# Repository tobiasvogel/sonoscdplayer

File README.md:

# SonosCDPlayer

**Your CDs, straight to Sonos.**

SonosCDPlayer is an open-source DIY project for building a standalone audio CD player that streams music to Sonos speakers over a local network.

It brings together the familiar experience of a physical CD player and the convenience of network audio: insert a disc, select your Sonos speakers, and control playback using dedicated buttons and a compact display.

The project uses readily available components, including a single-board computer, an optical drive, and configurable hardware controls. The long-term goal is a reliable, easy-to-use CD player that works without a smartphone or separate app during everyday operation.

## Project status

**Functional prototype — active development**

SonosCDPlayer is no longer just a concept. A working Python implementation exists, and its core audio, playback, Sonos, and hardware-interface functionality has been tested on real equipment.

Current capabilities include:

- **Live CD playback:** Read audio CDs and stream digital audio to Sonos over the local network.
- **Playback control:** Play, pause, resume, stop, next, and previous, including hardware-tested physical buttons.
- **Sonos integration:** Discover and select speakers, with controlled playback on individual devices and temporary speaker groups.
- **Display interface:** Show playback status, navigate menus, and select Sonos speakers using physical controls.
- **RAM-only audio buffering:** Stream CD audio using bounded memory without creating persistent audio copies.
- **Disc management:** Detect disc changes, handle verified USB drive reconnection, and eject discs using a physical button on tested hardware.
- **CD metadata and artwork:** Read CD-TEXT, retrieve MusicBrainz metadata, and store metadata and cover images in a local cache.
- **Wi-Fi setup:** Configure a network on the device or through a temporary setup hotspot.
- **System services:** Run the player and hardware interfaces through local services with configurable behaviour.

These foundations are implemented, but not every feature is enabled by default or validated across different hardware combinations. First-time setup, some device controls, broader hardware compatibility, and long-term reliability still require additional work.

**This is a working prototype, not yet a finished plug-and-play product or a complete beginner installation guide.**

## Design goals

- **Physical-first operation:** Dedicated controls and a display should make everyday playback feel like using a conventional CD player.
- **Local playback:** Play audio CDs through Sonos over the local network without requiring a cloud music service.
- **No ripping required:** Listen to physical CDs without first building a digital music library.
- **Respect existing Sonos playback:** Avoid unexpectedly interrupting other sources or changing unrelated speaker groups.
- **Accessible DIY hardware:** Use standard components and support different enclosure designs and hardware configurations.
- **Simple, maintainable software:** Prefer practical solutions, clear component boundaries, and predictable behaviour.

SonosCDPlayer is intended to be a dedicated CD player, not a general-purpose Sonos management system.

## How it works

The player reads digital audio from an inserted CD, buffers it in memory, and serves it as a WAV-compatible HTTP audio stream over the local network. The selected Sonos speaker or group retrieves this stream directly from the player.

```text
Audio CD -> Optical drive -> CD-DA reader -> Bounded RAM buffer
                                               |
                                               v
                                         Local HTTP server
                                               |
                                               v
                                         Sonos playback

Physical controls -> Player controller -> Display UI and menus
                              |
                              +-> Disc and drive management
                              |
                              +-> Sonos discovery and control
```

The player controller coordinates playback state, track navigation, disc handling, and Sonos control. Local interfaces allow hardware components to communicate with the player.

Audio is streamed as 44.1 kHz, 16-bit stereo PCM in a WAV-compatible format. The implementation includes buffering and HTTP range handling. Normal playback does not create persistent CD audio files.

## Hardware

SonosCDPlayer is designed around readily available components so builders can choose hardware that suits their needs and enclosure designs.

The software is developed and tested primarily on a Raspberry Pi 4 reference setup, while the architecture aims to accommodate different configurations.

A typical build consists of:

| Component | Purpose |
| --- | --- |
| Single-board computer (SBC), such as a Raspberry Pi | Runs the player software and network services |
| CD/DVD optical drive | Reads standard audio CDs |
| Sonos speaker or group | Receives and plays the CD audio stream |
| Display module | Shows playback information, device status, and menus |
| Physical controls (buttons and/or rotary encoder) | Control playback, navigate menus, and select options |
| Status LEDs (optional) | Provide additional visual feedback |
| Ambient light sensor (optional) | Enables automatic display and LED brightness adjustment |
| Power supply and enclosure | Complete the physical player |

### Hardware compatibility

The reference build combines physical buttons and a rotary encoder on a custom PCB, but alternative control layouts are a design goal. The repository also contains 3D-printable enclosure parts; a complete, tested assembly guide is still in preparation.

Reference optical drives are the **ASUS SDRW-08U1MT**, the **Panasonic/Matshita BD-MLT UJ265** and the **LG HL-DT-ST DVDRAM GTC0N**, each confirmed with the drive check below. Idle spin-down and wake-up were first verified with the ASUS drive connected through a powered USB hub. The **TSSTcorp CDDVDW TS-U633J** was also evaluated but proved unstable in the tested setup. These results are not an exhaustive compatibility list. To test another drive, run `python3 tools/check_drive.py` with an audio CD inserted; see [Checking a CD drive](docs/DRIVE_CHECK.md).

The [SonosCDPlayer website](https://sonoscdplayer.diy) is intended to collect tested components, hardware configurations, and community builds over time.

The goal is to support different builds, from simple functional prototypes to custom Hi-Fi components. Support for alternative SBCs, displays, and interfaces remains subject to implementation and testing.

## Playback and controls

SonosCDPlayer supports conventional CD playback controls through configurable physical input devices. The reference implementation combines dedicated buttons and a rotary encoder.

| Control | Behaviour |
| --- | --- |
| Play / Pause | Start, pause, or resume CD playback |
| Stop | Stop the player's CD playback and go back to track 1 |
| Next | Select or play the next track (stopped: counts up at once, without waking the drive) |
| Previous | Select or play the previous track (stopped: counts down at once, without waking the drive) |
| Eject | Open the drive tray when the required safety conditions are met |
| Volume + / − | Change the Sonos volume in steps of 1 (the whole group when grouped); hold to repeat. Works during the player's own playback, or before playback on a selected speaker that is not playing anything |
| Rotary encoder | Navigate the display interface |
| Encoder press | Confirm menu selections |

Physical playback buttons and disc ejection have been validated on reference hardware.

Volume buttons have been tested on reference hardware.

A Power button implementation provides a display-based power menu and long-press shutdown request. These system actions require explicit configuration.

**Important:** Hardware controls may run in diagnostic or preview modes unless their execution paths are enabled. A fresh installation does not automatically activate every available control function for now.

See [Power button](docs/POWER_BUTTON.md) for details.

## Sonos integration

SonosCDPlayer discovers available Sonos devices on the local network and provides a display-based interface for choosing a playback target.

Users can select an individual speaker or a combination of supported speakers. The player can create a temporary group for CD playback when the target devices are in an appropriate state. A disc-wide track queue enables navigation from the Sonos app; targeted hardware validation of the latest start and transition handling remains open.

Speaker selection and playback remain separate operations:

- Selecting speakers does not automatically start playback.
- The player checks the target state before taking control.
- Playback commands are restricted to the player's own active stream where appropriate.
- Unrelated playback sessions and groups must not be changed without explicit authorisation.
- Temporary groups created by the player are released again when playback ends; the player remembers them across restarts and cleans up a leftover of its own speakers at the next selection, PLAY or EJECT.
- A speaker chosen on the device that sits in an idle Sonos group (stopped or paused) is taken out of that group on its own; the rest of the group stays together. Groups that are playing are never changed.
- During playback, speakers can be added or removed in the device menu without interruption; choosing another main speaker restarts the current track on it. Changes made in the Sonos app are taken over and become the new speaker selection.
- Stereo pairs and home-theatre sets (Sub, surrounds) count as one speaker.

Individual-speaker playback and controlled group operation have been tested on real Sonos hardware. Compatibility with every Sonos model, firmware version, and network environment has not been established.

## Configuration

SonosCDPlayer uses **TOML configuration files** for software and hardware settings.

| File | Purpose |
| --- | --- |
| [`config/player.example.toml`](config/player.example.toml) | Audio streaming, optical drive management, and service settings |
| [`config/interface.example.toml`](config/interface.example.toml) | GPIO buttons, rotary encoder, and input behaviour |
| [`config/ui.example.toml`](config/ui.example.toml) | Display preferences and interface language |

The active configuration lives in **`/etc/sonoscdplayer/`** (`player.toml`, `interface.toml`, `ui.toml`); all services and tools read it from there. The repository files above are templates only. `tools/install_config.py` creates the files from the templates or migrates an existing configuration. See [Configuration files and location](docs/CONFIGURATION.md).

A configuration update utility offers dry-run checks, structural validation against an optional reference, backup creation, and rollback support. Perform service-affecting updates while the player is idle. See [Updating the player configuration](docs/CONFIG_UPDATE.md).

To join a Wi-Fi network, use the device menu to select a network and enter its password, or hold CONNECT for 10 seconds to open a temporary setup hotspot with a web page. Both methods have been tested on reference hardware; additional failure and timeout scenarios remain open. See [Wi-Fi setup](docs/NETWORK_SETUP.md).

## Display and languages

SonosCDPlayer provides a display-based interface for playback information, device status, and menu navigation.

The player supports the SSD1327 grayscale OLED and SSD1351 RGB OLED through the same `[display]` configuration. Both 128x128 modules have been tested on hardware; see [Display configuration](docs/DISPLAY_CONFIGURATION.md) and [SSD1351](docs/SSD1351.md). Drivers and test tools for a smaller monochrome OLED (SH1107) and a color LCD (ST7735S) are included and await their connection to the player; a four-color e-paper module was evaluated and found unsuitable. See [Displays](docs/DISPLAYS.md).

The implemented interface includes playback and disc status, interactive menus, Sonos target selection, and rotary encoder navigation. English and German are available; the selected language is retained across restarts in local application state. Adaptive brightness is supported on suitable reference hardware.

CD-TEXT, MusicBrainz metadata and album artwork on the reference OLED are implemented and have been tested on hardware. Further interface improvements and metadata edge-case testing remain open.

See [Display languages and translations](docs/I18N.md) for details.

## Development roadmap

The roadmap distinguishes working foundations from features still under development or awaiting broader validation.

### Working foundations

- [x] Detect audio CDs and read track information on reference hardware.
- [x] Stream live CD audio to a real Sonos device.
- [x] Implement bounded RAM-only audio buffering.
- [x] Implement playback state management and track navigation.
- [x] Provide a persistent player service and local control interface.
- [x] Implement Sonos discovery, target selection, and controlled temporary group playback.
- [x] Implement an interactive display interface with playback status and menus, validated on reference OLED hardware.
- [x] Implement and hardware-test physical playback buttons.
- [x] Detect disc changes and handle verified optical drive reconnection.
- [x] Implement and hardware-test physical disc ejection on reference hardware.
- [x] Verify optical-drive idle spin-down and wake-up using a powered USB hub on reference hardware.
- [x] Implement and hardware-test CD-TEXT, MusicBrainz lookup, and local metadata and cover caching.
- [x] Implement and hardware-test device-based Wi-Fi selection and setup hotspot.

### Work in progress and planned features

- [ ] Complete hardware validation of remaining device controls and their integration.
- [ ] Validate optical-drive idle spin-down and wake-up over extended operation and on additional hardware.
- [ ] Complete boot, shutdown, restart, and long-term reliability testing.
- [ ] Validate remaining Wi-Fi setup failure, timeout, and recovery scenarios.
- [ ] Complete hardware tests for disc-wide Sonos navigation and remaining metadata edge cases.
- [ ] Expand and validate support for additional hardware configurations and interchangeable interfaces.
- [ ] Publish reproducible installation instructions and a hardware compatibility guide.
- [ ] Provide a complete bill of materials, wiring documentation, and a tested build guide.

Completed items represent implemented and tested foundations, not universal hardware compatibility or completion of every related enhancement.

## Documentation

Additional documentation is available in the [`docs/`](docs/) directory.

| Document | Description |
| --- | --- |
| [Configuration files and location](docs/CONFIGURATION.md) | Standard location, installation, migration, and systemd units |
| [Configuration updates](docs/CONFIG_UPDATE.md) | TOML configuration checks, replacement, and rollback |
| [Display languages and translations](docs/I18N.md) | Language selection and adding translations |
| [Wi-Fi setup](docs/NETWORK_SETUP.md) | Joining a new Wi-Fi network through the setup hotspot |
| [Power button](docs/POWER_BUTTON.md) | Power controls, permissions, and activation |
| [Shutdown and restart screens](docs/SHUTDOWN_SCREENS.md) | OLED screens while shutting down or restarting, installation, optional exitrd |
| [Status LEDs](docs/STATUS_LEDS.md) | Meaning of the power and connection (network) LEDs |
| [Checking a CD drive](docs/DRIVE_CHECK.md) | Test whether a USB CD drive suits the player and share the result |
| [Displays](docs/DISPLAYS.md) | Supported and evaluated modules; [configuration](docs/DISPLAY_CONFIGURATION.md), [SSD1351](docs/SSD1351.md), [SH1107](docs/SH1107.md) and [ST7735S](docs/ST7735S.md) |
| [Architecture](docs/ARCHITECTURE.md) | Services, sockets, data flow and package layout, for developers |
| [Adding a display](docs/ADDING_A_DISPLAY.md) | Driver, test program, renderer and tests for a new display module |
| [Adding buttons and input modules](docs/ADDING_INPUTS.md) | New buttons, shift registers or other input modules, rotary encoder |
| [Releases and updates](docs/RELEASE.md) | Version number, making a release, updating the device |
| [Changelog](CHANGELOG.md) | Changes per version |

Some features are optional or hardware-specific. Consult each guide for its requirements and limitations.

## Contributing

Contributions are welcome, including software improvements, hardware compatibility reports, testing feedback, translations, wiring diagrams, documentation, and enclosure designs.

The Python code is one package, `src/sonoscdplayer/`, organized by area: `audio` (reading and streaming the CD), `drive` (the optical drive), `metadata`, `sonos`, `player` (the player service), `ui` (the display service and menu), `hardware` (displays, buttons, LEDs, sensors), `network_setup` and `system`. Native C code is in `src/native/`. Tests mirror the package under `tests/` and run with `python3 -m pytest`. Every public module, class and function has a docstring (Google style); run `tools/build_api_docs.sh` to turn them into an HTML code reference in `docs/api/` with [pdoc](https://pdoc.dev) (Debian package `python3-pdoc`, installed by `scripts/setup.sh`). Start with the [architecture overview](docs/ARCHITECTURE.md).

For substantial code changes, please open an issue describing the proposed improvement or problem before beginning work. The project favours maintainable implementations and incremental, hardware-backed testing.

Do not commit credentials, private network information, personal Sonos device identifiers, local configuration files containing private details, or copyrighted CD audio recordings.

## License

See [LICENSE](LICENSE) for the repository's GNU General Public License version 2 license text.

## Project links

**Website:** https://sonoscdplayer.diy  
**GitHub:** https://github.com/tobiasvogel/sonoscdplayer

## Disclaimer

SonosCDPlayer is an independent open-source community project and is not affiliated with, endorsed by, or sponsored by Sonos, Inc. Sonos is a trademark of its respective owner.

Hardware compatibility depends on the components, software versions, and network environment used. Not every configuration has been tested.

Product-style illustrations and renderings are conceptual unless explicitly identified as photographs of a tested build.

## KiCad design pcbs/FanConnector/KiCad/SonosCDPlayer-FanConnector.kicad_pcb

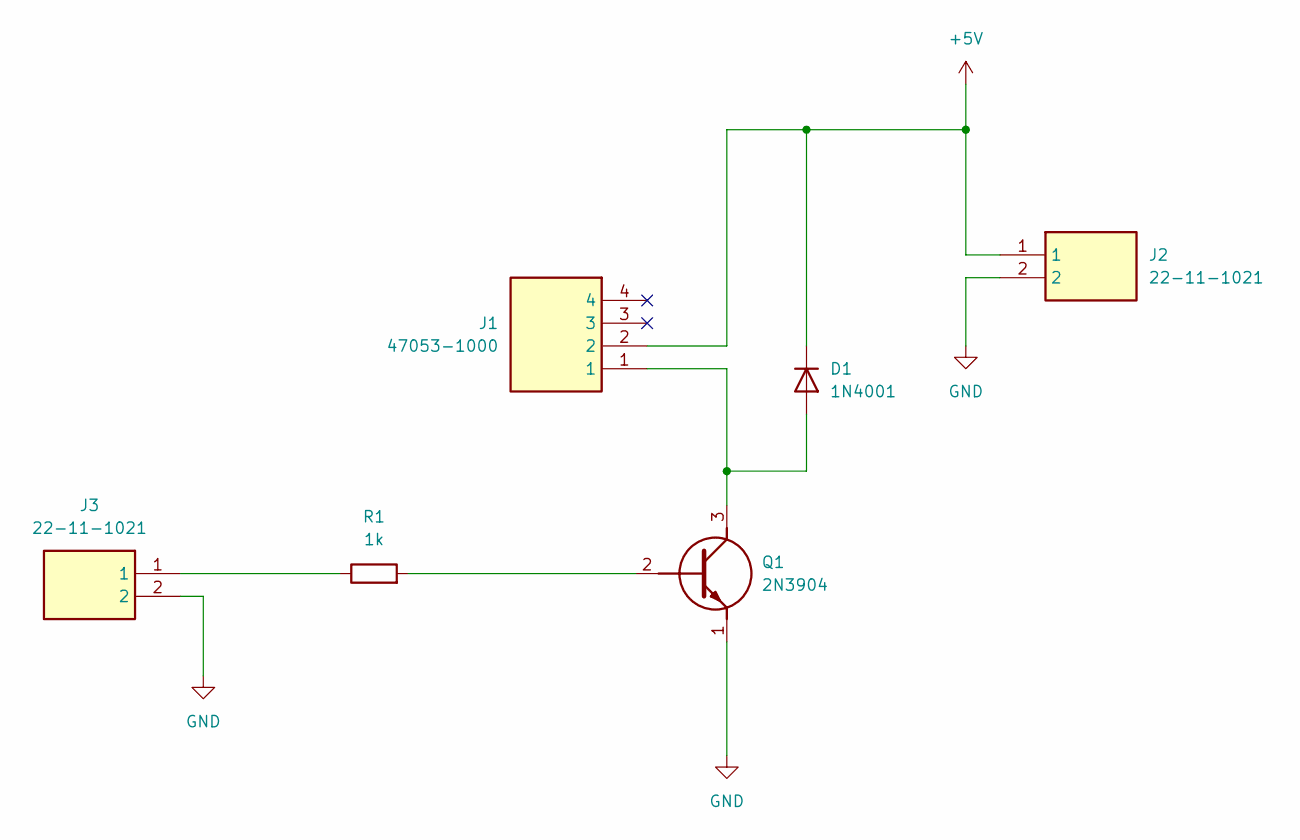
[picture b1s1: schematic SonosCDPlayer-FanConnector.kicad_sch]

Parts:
D1: 1N4001; D_DO-41_SOD81_P10.16mm_Horizontal
J1: 47053-1000; 470531000; Mouser Part Number 538-47053-1000
J2, J3: 22-11-1021; HDRV2W64P0X250_1X2_450X490X1105P; Mouser Part Number 538-22-11-1021
Q1: 2N3904; Mouser Part Number 637-2N3904
R1: 1k; R_Axial_DIN0207_L6.3mm_D2.5mm_P10.16mm_Horizontal

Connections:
+5V: D1.1 (K), J1.2, J2.1
GND: J2.2, J3.2, Q1.1 (E)
unnamed: D1.2 (A), J1.1, Q1.3 (C)
unnamed: J3.1, R1.1
unnamed: Q1.2 (B), R1.2

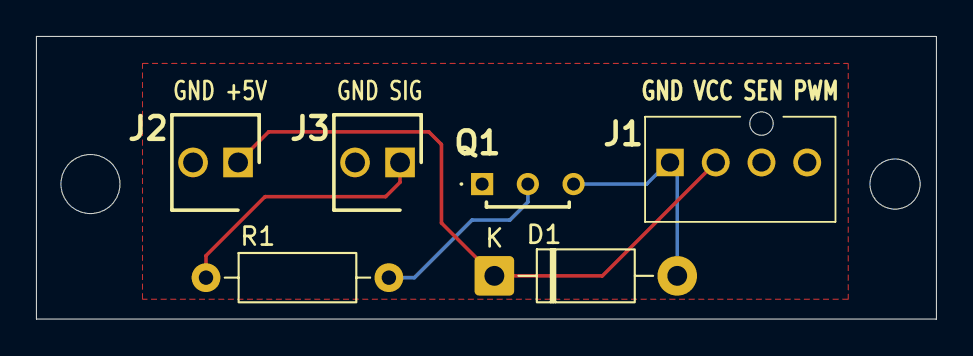
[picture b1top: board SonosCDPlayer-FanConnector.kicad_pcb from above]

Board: 2 copper layers, 50.0 x 15.7 mm, 6 parts (0 on the bottom side), 5 nets.

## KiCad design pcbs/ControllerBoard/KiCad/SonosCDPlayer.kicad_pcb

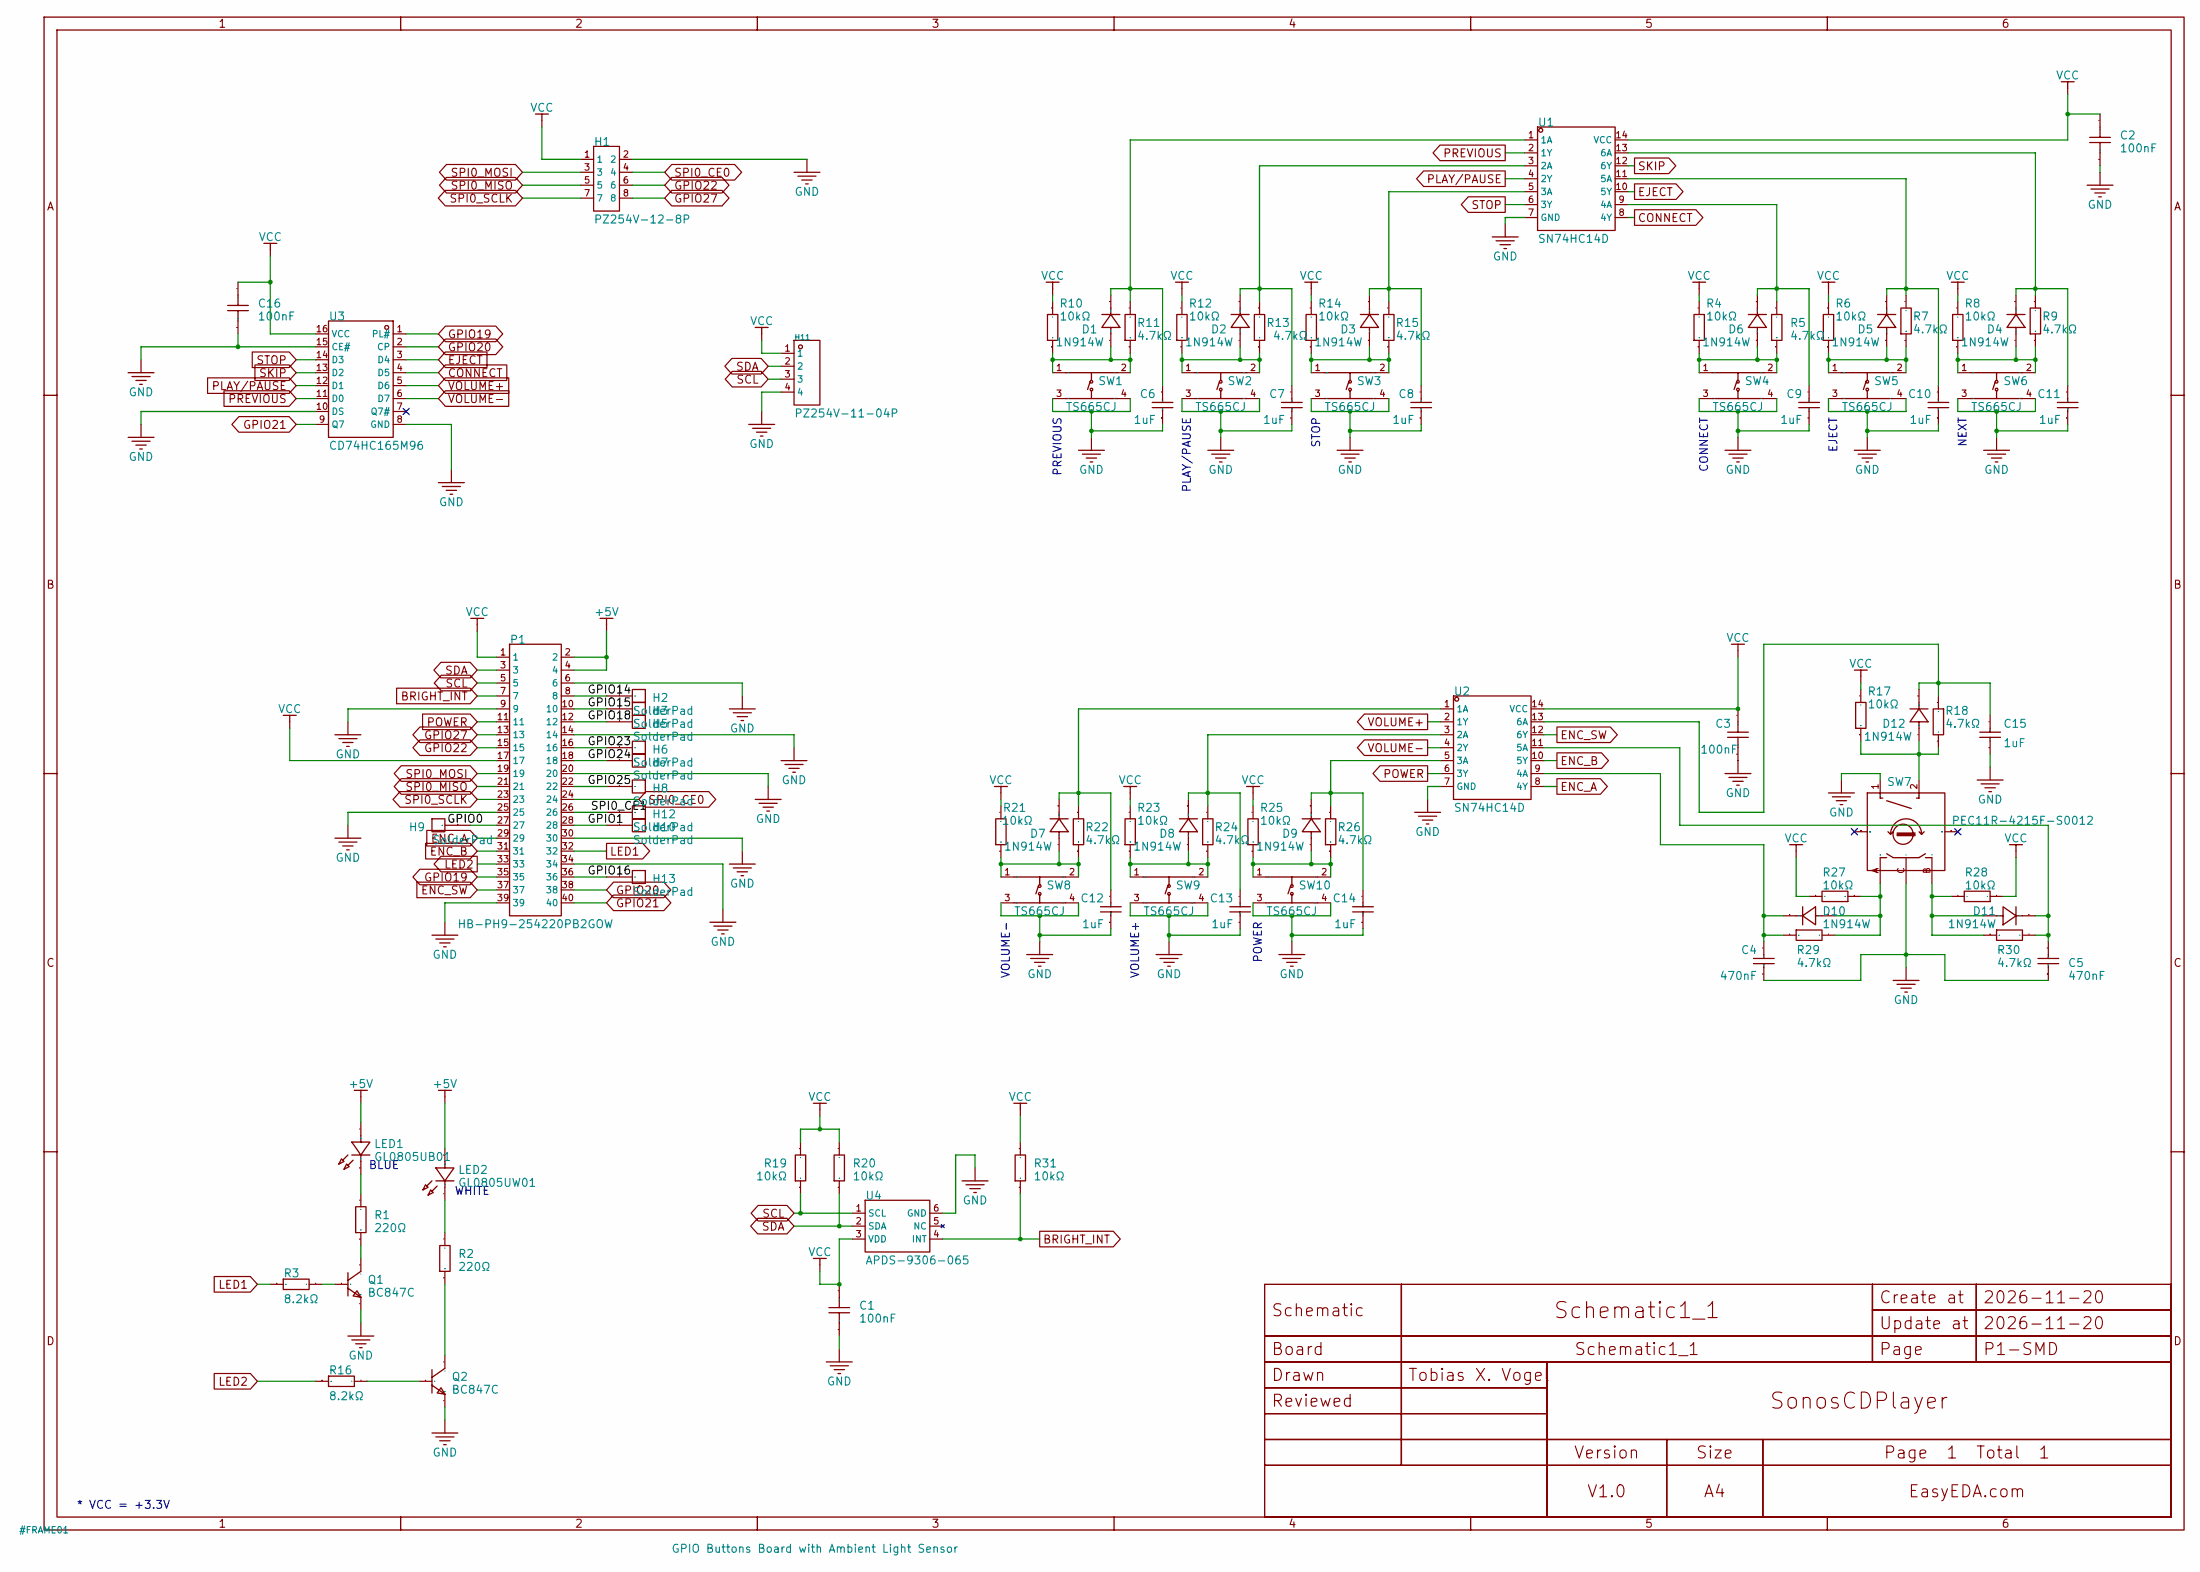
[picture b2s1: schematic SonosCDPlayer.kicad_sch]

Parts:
C1, C2, C3, C16: 100nF; C0805; Tolerance ±10%; Voltage Rating 50V; Manufacturer Part FCC0805B104K500DT; LCSC Part Name 100nF ±10% 50V
C4, C5: 470nF; C0805; Tolerance ±10%; Voltage Rating 50V; Manufacturer Part CC0805KKX7R9BB474; LCSC Part Name 470nF ±10% 50V
C6, C7, C8, C9, C10, C11, C12, C13, C14, C15: 1uF; C0805; Tolerance ±10%; Voltage Rating 16V; Manufacturer Part CL21B105KOFNNNE; LCSC Part Name 1uF ±10% 16V
D1, D2, D3, D4, D5, D6, D7, D8, D9, D10, D11, D12: 1N914W; SOD-123_L2.7-W1.6-LS3.7-RD-1; Voltage - DC Reverse(Vr) 100V; Voltage - Forward(Vf@If) 1V@10mA; Manufacturer Part 1N914W; LCSC Part Name T4(T4表示丝印) 200mA 100V
H1: PZ254V-12-8P; HDR-TH_8P-P2.54-V-M-R2-C4-S2.54; Manufacturer Part PZ254V-12-8P; LCSC Part Name 2x4P 间距:2.54mm 方针 直插
H2, H3, H5, H6, H7, H8, H9, H10, H12, H13: SolderPad; HDR-TH_1P-P2.54-V-F
H11: PZ254V-11-04P; HDR-TH_4P-P2.54-V-M; Manufacturer Part PZ254V-11-04P; LCSC Part Name 1x4P 间距:2.54mm 方针 直插
LED1: GL0805UB01; LED0805-RD_BLUE; Voltage - Forward(Vf) 2.6V~3.1V; Manufacturer Part GL0805UB01; LCSC Part Name 0805 蓝灯 高亮
LED2: GL0805UW01; LED-SMD_L2.0-W1.3-R-RD; Voltage - Forward(Vf) 2.6V~3V; Manufacturer Part GL0805UW01; LCSC Part Name 0805 白灯 高亮
P1: HB-PH9-254220PB2GOW; CONN-SMD_HB-PH9-254220PB2GOW; Current Rating 3A; Manufacturer Part HB-PH9-254220PB2GOW; LCSC Part Name 2x20P 间距:2.54mm 方针 立贴
Q1, Q2: BC847C; SOT-23-3_L3.0-W1.7-P0.95-LS2.9-BR; Manufacturer Part BC847C; LCSC Part Name NPN 电流:0.1A 电压:45V
R1, R2: 220Ω; R0805; Tolerance ±1%; Voltage-Supply(Max) 150V; Manufacturer Part RC0805FR-07220RL; LCSC Part Name 厚膜电阻 220Ω ±1% 125mW
R3, R16: 8.2kΩ; R0805; Tolerance ±1%; Voltage-Supply(Max) 150V; Manufacturer Part RC0805FR-078K2L; LCSC Part Name 厚膜电阻 8.2kΩ ±1% 125mW
R4, R6, R8, R10, R12, R14, R17, R19, R20, R21, R23, R25, R27, R28, R31: 10kΩ; R0805; Tolerance ±5%; Manufacturer Part RC0805JR-0710KL; LCSC Part Name 厚膜电阻 10kΩ ±5% 125mW
R5, R7, R9, R11, R13, R15, R18, R22, R24, R26, R29, R30: 4.7kΩ; R0805; Tolerance ±1%; Voltage-Supply(Max) 150V; Manufacturer Part RC0805FR-074K7L; LCSC Part Name 厚膜电阻 4.7kΩ ±1% 125mW
SW1, SW2, SW3, SW4, SW5, SW6, SW8, SW9, SW10: TS665CJ; SW-TH_4P-L6.0-W6.0-P4.50-LS6.5; Voltage Rating 12V; Manufacturer Part TS665CJ; LCSC Part Name 6*6*5mm 直插 轻触开关
SW7: PEC11R-4215F-S0012; SW-TH_PEC11R-4XXXF-SXXXX; Current Rating (Max) 10mA; Rated Voltage (Max) 5V; Manufacturer Part PEC11R-4215F-S0012; LCSC Part Name 3件套 12mm增量编码器
U1, U2: SN74HC14D; SOIC-14_L8.7-W3.9-P1.27-LS6.0-BL; Voltage - Supply 2V~6V; Manufacturer Part SN74HC14D; LCSC Part Name 停产 六路施密特触发反相器
U3: CD74HC165M96; SOIC-16_L9.9-W3.9-P1.27-LS6.0-BL; Voltage - Supply 2V~6V; Manufacturer Part CD74HC165M96; LCSC Part Name 补充型输出 8位并行或串行至串行移位寄存器
U4: APDS-9306-065; SENSOR-SMD_RAPDS-9306-065; Manufacturer Part APDS-9306-065; LCSC Part Name 微型表面贴装数字环境光传感器

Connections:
+5V: LED1.2 (A), LED2.1 (A), P1.2, P1.4
/GPIO0: H9.1, P1.27
/GPIO1: H10.1, P1.28
/GPIO14: H2.1, P1.8
/GPIO15: H3.1, P1.10
/GPIO16: H13.1, P1.36
/GPIO18: H5.1, P1.12
/GPIO23: H6.1, P1.16
/GPIO24: H7.1, P1.18
/GPIO25: H8.1, P1.22
/SPI0_CE1: H12.1, P1.26
BRIGHT_INT: P1.7, R31.1, U4.4 (INT)
CONNECT: U1.8 (4Y), U3.4 (D5)
EJECT: U1.10 (5Y), U3.3 (D4)
ENC_A: P1.29, U2.8 (4Y)
ENC_B: P1.31, U2.10 (5Y)
ENC_SW: P1.37, U2.12 (6Y)
GND: C1.1, C2.1, C3.1, C4.1, C5.1, C6.1, C7.1, C8.1, C9.1, C10.1, C11.1, C12.1, C13.1, C14.1, C15.1, C16.1, H1.2, H11.4, P1.6, P1.9, P1.14, P1.20, P1.25, P1.30, P1.34, P1.39, Q1.2 (E), Q2.2 (E), SW1.3 (C), SW1.4 (D), SW2.3 (C), SW2.4 (D), SW3.3 (C), SW3.4 (D), SW4.3 (C), SW4.4 (D), SW5.3 (C), SW5.4 (D), SW6.3 (C), SW6.4 (D), SW7.1, SW7.C, SW8.3 (C), SW8.4 (D), SW9.3 (C), SW9.4 (D), SW10.3 (C), SW10.4 (D), U1.7 (GND), U2.7 (GND), U3.8 (GND), U3.10 (DS), U3.15 (CE#), U4.6 (GND)
GPIO19: P1.35, U3.1 (PL#)
GPIO20: P1.38, U3.2 (CP)
GPIO21: P1.40, U3.9 (Q7)
GPIO22: H1.6, P1.15
GPIO27: H1.8, P1.13
LED1: P1.32, R3.1
LED2: P1.33, R16.1
unnamed: D1.2 (A), R10.1, R11.1, SW1.1 (A), SW1.2 (B)
unnamed: C6.2, D1.1 (K), R11.2, U1.1 (1A)
unnamed: D2.2 (A), R12.1, R13.1, SW2.1 (A), SW2.2 (B)
unnamed: C7.2, D2.1 (K), R13.2, U1.3 (2A)
unnamed: D3.2 (A), R14.1, R15.1, SW3.1 (A), SW3.2 (B)
unnamed: C8.2, D3.1 (K), R15.2, U1.5 (3A)
unnamed: D4.2 (A), R8.1, R9.1, SW6.1 (A), SW6.2 (B)
unnamed: C11.2, D4.1 (K), R9.2, U1.13 (6A)
unnamed: D5.2 (A), R6.1, R7.1, SW5.1 (A), SW5.2 (B)
unnamed: C10.2, D5.1 (K), R7.2, U1.11 (5A)
unnamed: D6.2 (A), R4.1, R5.1, SW4.1 (A), SW4.2 (B)
unnamed: C9.2, D6.1 (K), R5.2, U1.9 (4A)
unnamed: D7.2 (A), R21.1, R22.1, SW8.1 (A), SW8.2 (B)
unnamed: C12.2, D7.1 (K), R22.2, U2.1 (1A)
unnamed: D8.2 (A), R23.1, R24.1, SW9.1 (A), SW9.2 (B)
unnamed: C13.2, D8.1 (K), R24.2, U2.3 (2A)
unnamed: D9.2 (A), R25.1, R26.1, SW10.1 (A), SW10.2 (B)
unnamed: C14.2, D9.1 (K), R26.2, U2.5 (3A)
unnamed: D10.2 (A), R27.1, R29.2, SW7.A
unnamed: C4.2, D10.1 (K), R29.1, U2.9 (4A)
unnamed: D11.2 (A), R28.2, R30.1, SW7.B
unnamed: C5.2, D11.1 (K), R30.2, U2.11 (5A)
unnamed: D12.2 (A), R17.1, R18.2, SW7.2
unnamed: C15.2, D12.1 (K), R18.1, U2.13 (6A)
unnamed: LED1.1 (K), R1.2
unnamed: LED2.2 (C), R2.2
unnamed: Q1.1 (B), R3.2
unnamed: Q1.3 (C), R1.1
unnamed: Q2.1 (B), R16.2
unnamed: Q2.3 (C), R2.1
PLAY/PAUSE: U1.4 (2Y), U3.12 (D1)
POWER: P1.11, U2.6 (3Y)
PREVIOUS: U1.2 (1Y), U3.11 (D0)
SCL: H11.3, P1.5, R19.1, U4.1 (SCL)
SDA: H11.2, P1.3, R20.1, U4.2 (SDA)
SKIP: U1.12 (6Y), U3.13 (D2)
SPI0_CE0: H1.4, P1.24
SPI0_MISO: H1.5, P1.21
SPI0_MOSI: H1.3, P1.19
SPI0_SCLK: H1.7, P1.23
STOP: U1.6 (3Y), U3.14 (D3)
VCC: C1.2, C2.2, C3.2, C16.2, H1.1, H11.1, P1.1, P1.17, R4.2, R6.2, R8.2, R10.2, R12.2, R14.2, R17.2, R19.2, R20.2, R21.2, R23.2, R25.2, R27.2, R28.1, R31.2, U1.14 (VCC), U2.14 (VCC), U3.16 (VCC), U4.3 (VDD)
VOLUME+: U2.2 (1Y), U3.5 (D6)
VOLUME-: U2.4 (2Y), U3.6 (D7)

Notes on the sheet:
STOP
* VCC = +3.3V
NEXT
VOLUME-
EJECT
WHITE
CONNECT
BLUE
PLAY/PAUSE
PREVIOUS
POWER
VOLUME+

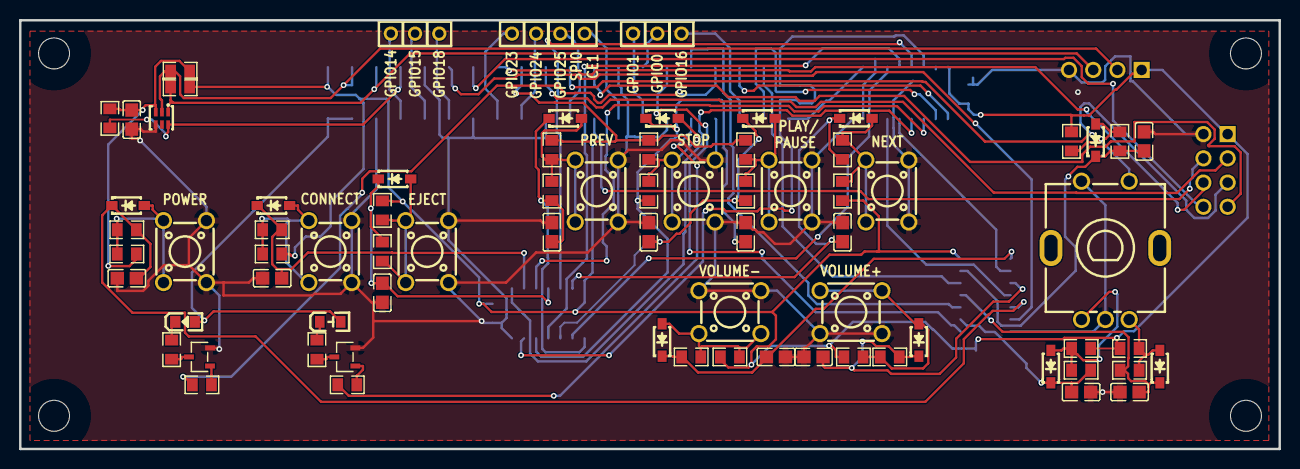
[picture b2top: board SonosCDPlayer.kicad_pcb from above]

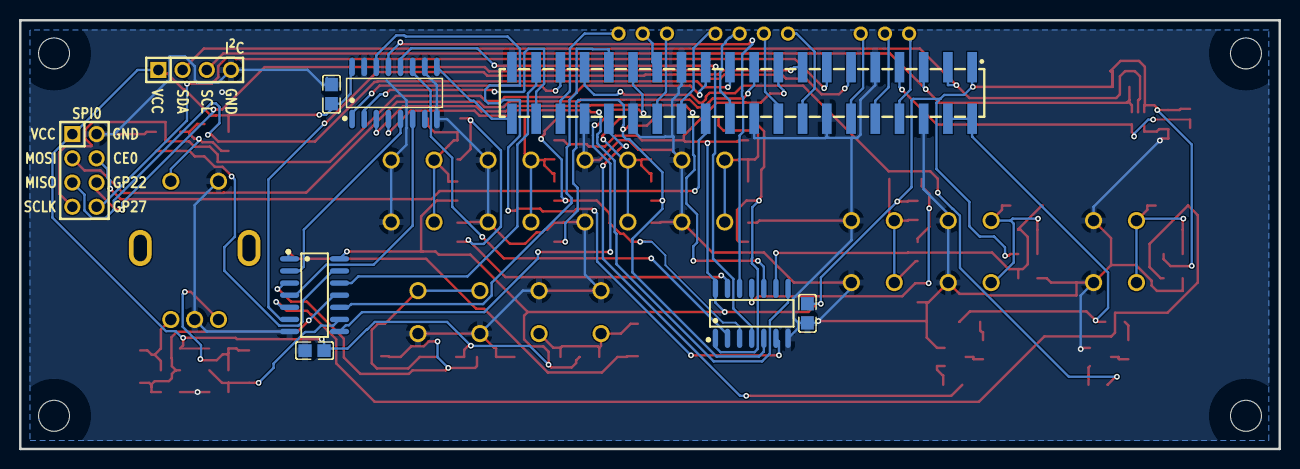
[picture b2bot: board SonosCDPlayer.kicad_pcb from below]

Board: 2 copper layers, 132.1 x 45.0 mm, 90 parts (9 on the bottom side), 69 nets.
